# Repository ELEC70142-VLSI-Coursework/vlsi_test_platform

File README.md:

# VLSI Test Platform

A complete hardware and software solution for bringing up and testing the VLSI SoC Project IC. This repository contains the FPGA firmware, Python host tools, and hardware design documentation.

## System Overview

The test platform consists of three integrated components:

<div align="center">
    
</div>

## Directory Structure

```
vlsi_test_platform/
├── gw/                    # FPGA Firmware (DE10-Lite)
│   ├── src/              # SystemVerilog modules
│   │   ├── DE10Top.sv    # Top-level module
│   │   ├── jtag_uart_bridge.sv
│   │   ├── jtag_engine.sv
│   │   ├── adc_commander.sv
│   │   ├── i2c_master.sv
│   │   └── uart_*.sv     # UART controller modules
│   ├── test/             # DUT (Device Under Test) bitstreams
│   └── README.md         # FPGA documentation
│
├── sw/                    # Host-Side Python Tools
│   ├── JTAGProg.py       # JTAG programmer and tester
│   └── README.md         # Python tool documentation
│
├── hw/                    # Test Board PCB Design
│   ├── [Schematic/Layout files]
│   └── README.md         # Hardware documentation
│
└── README.md             # This file
```

## Quick Start

### Prerequisites

1. **Hardware**: DE10-Lite FPGA board and VLSI test board
2. **Software**: Quartus Prime, Python 3.6+, pyserial

### 1. Program the FPGA

1. Load the compiled FPGA design (`.sof` file) onto the DE10-Lite using Quartus Programmer
2. The FPGA automatically configures the test board DAC after reset
3. Verify that the USB-UART bridge is recognized on your host computer

### 2. Program the IC via JTAG

```bash
# Test mode: verify JTAG communication with a known pattern
python JTAGProg.py COM4 --test-mode --word-count 256

# Load mode: program memory from a hex file
python JTAGProg.py COM4 program.hex
```

See [sw/README.md](sw/README.md) for full usage details.

### 3. Verify the Setup

- Check that the test board LEDs indicate correct power and USB connection
- Monitor JTAG read/write throughput in the python interface output
- Inspect the IC power supplies and clock signals with an oscilloscope if needed

## Component Details

### FPGA Firmware (gw/)

The DE10-Lite FPGA implements:
- **UART-to-JTAG Bridge**: Converts serial bytes to JTAG protocol for IC programming
- **I2C Master**: Configures the DAC for PLL bias voltages
- **Clock Generator**: Produces a test clock output

[Read more](gw/README.md)

### Python Host Tool (sw/)

`JTAGProg.py` provides:
- **Test Mode**: Random write/read verification for JTAG communication
- **Load Mode**: Program IC memory from a plain-text hex file
- **Performance Monitoring**: Reports read/write throughput and errors

[Read more](sw/README.md)

### Test Board Hardware (hw/)

The PCB includes:
- PLCC socket for the VLSI IC
- Power management (3.3 V and 1.2 V LDOs)
- DAC for PLL bias voltage tuning
- USB-to-UART bridge (CP2102N)
- FPGA connector for control signals (JTAG, I2C, clock)
- Reset button and DIP switch for PLL frequency selection

[Read more](hw/README.md)

## References

- Altera DE10-Lite Board: [User Manual](https://www.intel.com/content/www/us/en/programmable/documentation/boards/de10_lite_user_manual.pdf)
- CP2102N USB-UART IC: [Datasheet](https://www.silabs.com/documents/public/data-sheets/cp2102n-datasheet.pdf)
- DAC7578 DAC IC: [Datasheet](https://www.ti.com/lit/ds/symlink/dac7578.pdf?ts=1773684272389&ref_url=https%253A%252F%252Fwww.ti.com%252Fproduct%252FDAC7578)

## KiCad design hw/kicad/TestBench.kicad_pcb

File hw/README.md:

# Testboard Hardware

The testboard is an integrated solution for the **VLSI SoC Project** IC bring-up. It includes:

- PLCC socket
- LDOs for the padring and core supplies (3.3 V and 1.2 V respectively)
- Reset button
- Solderable jumper to select active-high or active-low reset
- 25 MHz crystal oscillator
- DAC to supply bias voltages to the PLL
- 4-position DIP switch for selecting the PLL frequency
- USB-to-UART bridge IC (CP2102N)
- Jumpers to select the source of the clock and 1.2 V supply (board or connector)
- Buffers for the FPGA input clock and the board output clock
- Connector for the DE10-Lite FPGA

<div align="center">
    
</div>

## Assembly Guidelines

First, solder the SMD components using the stencil and a reflow oven. Do not place the DIP switch in the reflow oven — solder it by hand afterwards.

Once the SMD components are soldered, test the LDOs by applying 5 V and 3.3 V to connector U1 (TB). Check for shorts on the USB-C connector and verify that QFN packages U5 and U6 have no solder bridges and all pins are properly soldered. 

Set solder jumpers JP4 and JP5 to the low position, marked "L" on the silkscreen.

Next, solder the through-hole components: power switch S2, connector J2, jumpers JP1 and JP2, and the 40-pin FPGA connectors. Do not solder the PLCC socket (J4) at this stage — leaving it unsoldered allows easier access to the pin holes for testing.

Once testing is complete, solder the PLCC socket with the orientation arrow pointing down, indicating pin 1.

### Testing the DAC

The I2C DAC IC can be tested by connecting a DE10-Lite FPGA board and loading the bitstream described elsewhere in this repository. The FPGA automatically configures the DAC over I2C after reset. The DAC requires the 1.2 V supply as its reference — ensure the core-supply jumper is set to "BRD" to use the onboard LDO. Measure the DAC outputs at testpoints DAC1 and DAC2; the expected voltages are defined in [gw/src/adc_commander.sv](../gw/src/adc_commander.sv).

### Testing the USB-UART Bridge

Test the USB-UART bridge using the provided FPGA design (see elsewhere in this repository). After loading the bitstream, verify UART–JTAG communication using the Python script.

The TX/RX LEDs (D2 and D3) will not function on a newly soldered CP2102N until the IC has been configured. To configure it:

1. Install the USB-to-UART VCP drivers from [Silicon Labs](https://www.silabs.com/software-and-tools/usb-to-uart-bridge-vcp-drivers?tab=downloads).
2. Install [Simplicity Studio 5](https://www.silabs.com/software-and-tools/simplicity-studio/simplicity-studio-version-5) (not version 6).
3. Power the board and launch Simplicity Studio — it should detect the CP2102N automatically.
4. Open **Tools > Express Configurator**.
5. Under **Configuration Groupings > Port Configurations > GPIO**, set GPIO0 to "TX Toggle" and GPIO1 to "RX Toggle".
6. Click **Program to Device**.

## Suggested Improvements

Future board revisions could include:

- Decoupling capacitors between the PLCC socket supply pins and ground.
- A silkscreen mark indicating PLCC socket pin 1.
- A small series resistor between the PLCC socket clock input and the Schmitt-trigger buffer to reduce ringing.
- Additional mounting holes.

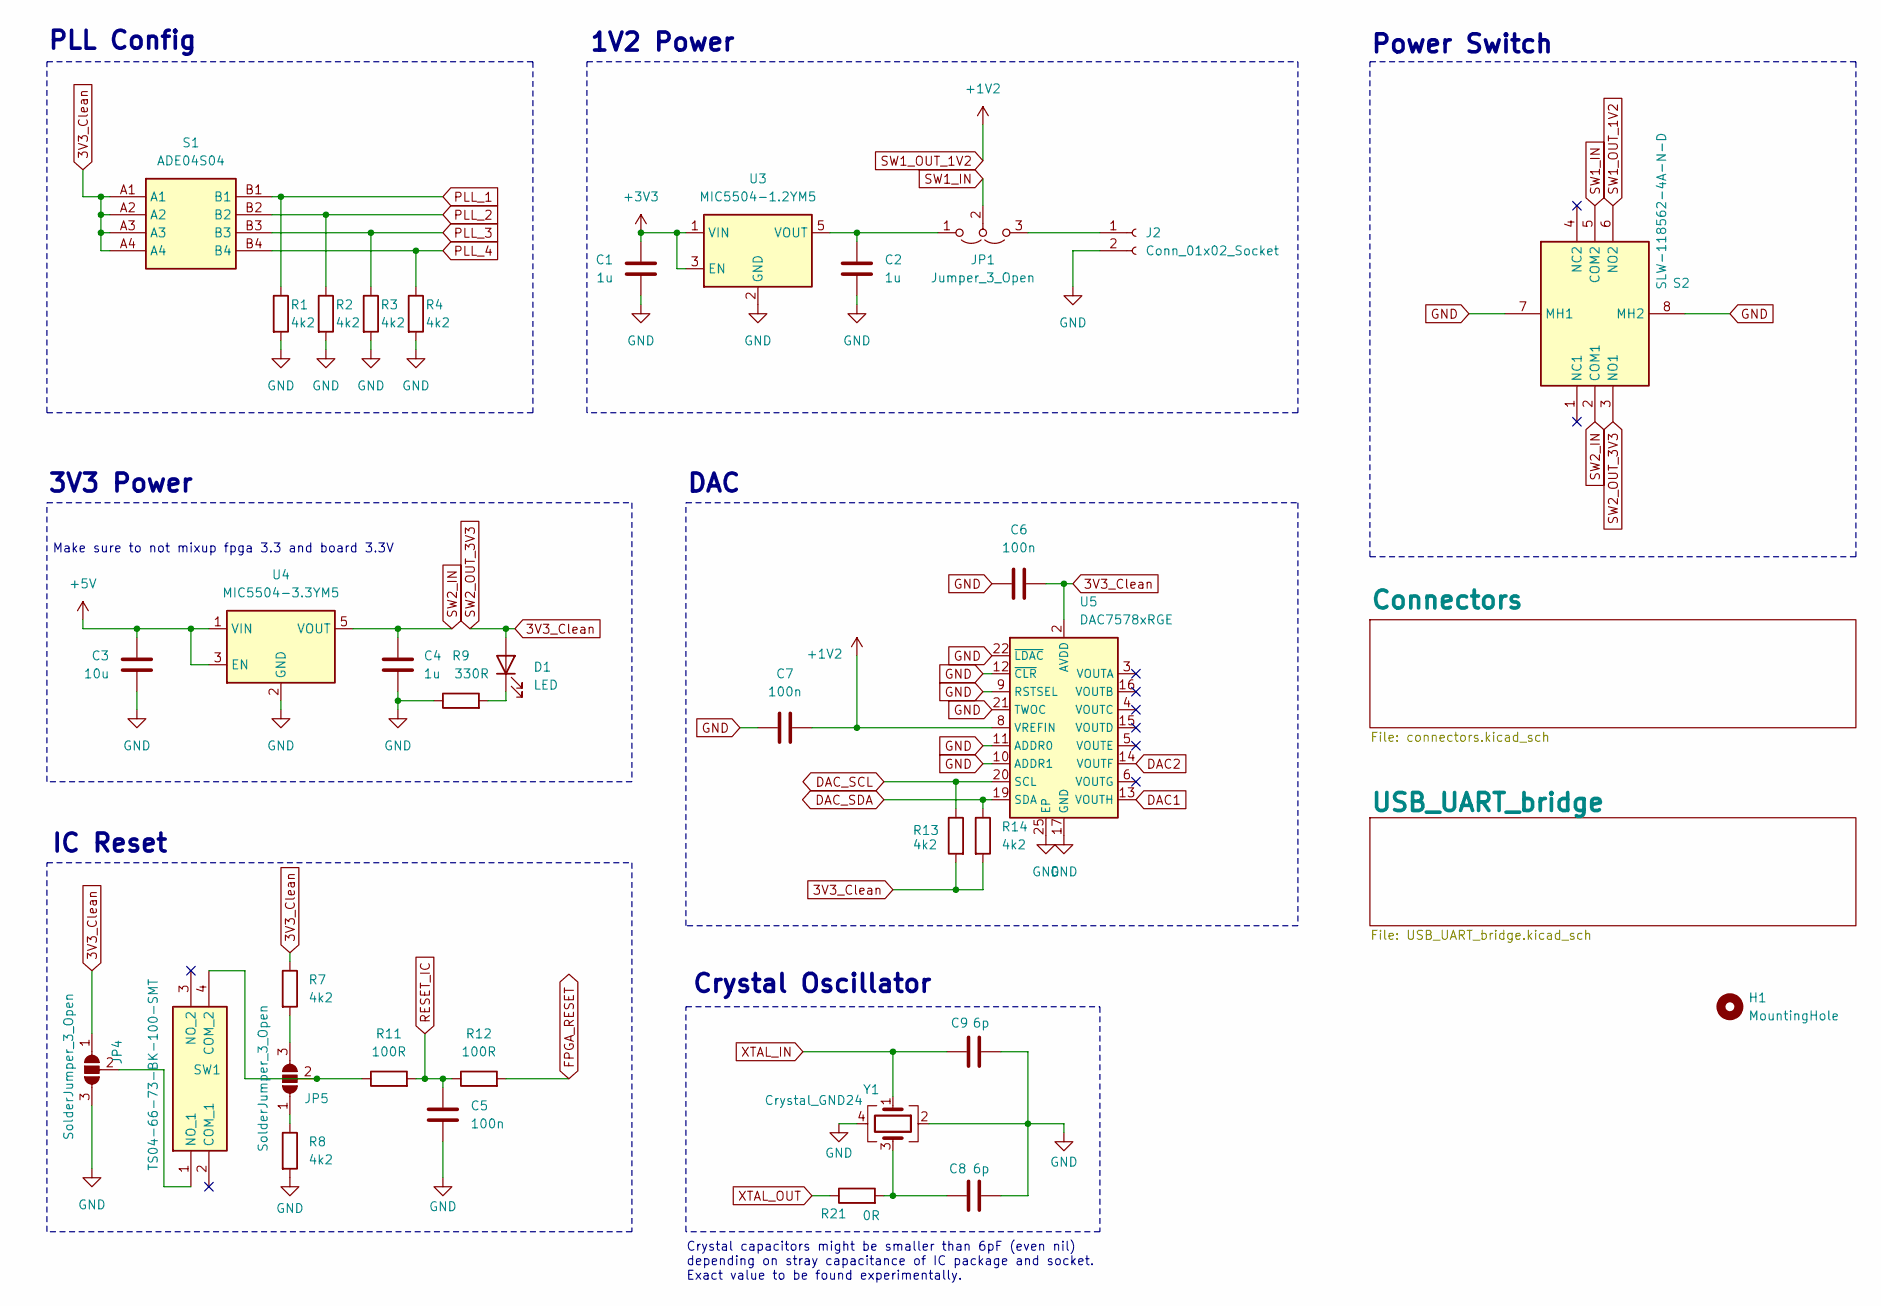
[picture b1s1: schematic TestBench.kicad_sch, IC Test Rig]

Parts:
C1, C2, C4: 1u; C_0805_2012Metric_Pad1.18x1.45mm_HandSolder
C3: 10u; C_0805_2012Metric_Pad1.18x1.45mm_HandSolder
C5, C6, C7: 100n; C_0805_2012Metric_Pad1.18x1.45mm_HandSolder
C8, C9: 6p; C_0805_2012Metric_Pad1.18x1.45mm_HandSolder
D1: LED; LED_0805_2012Metric_Pad1.15x1.40mm_HandSolder
H1: MountingHole; MountingHole_3.2mm_M3
J2: Conn_01x02_Socket; CTB30512BK
JP1: Jumper_3_Open; PinHeader_1x03_P2.54mm_Vertical
JP4, JP5: SolderJumper_3_Open; SolderJumper-3_P1.3mm_Open_RoundedPad1.0x1.5mm
R1, R2, R3, R4, R7, R8, R13, R14: 4k2; R_0805_2012Metric_Pad1.20x1.40mm_HandSolder
R9: 330R; R_0805_2012Metric_Pad1.20x1.40mm_HandSolder
R11, R12: 100R; R_0805_2012Metric_Pad1.20x1.40mm_HandSolder
R21: 0R; R_0805_2012Metric_Pad1.20x1.40mm_HandSolder
S1: ADE04S04; Mouser Part Number 506-ADE04S04
S2: SLW-118562-4A-N-D; SLW1185624AND; Mouser Part Number 179-SLW1185624AND
SW1: TS04-66-73-BK-100-SMT; TS046665BK160SMT; Mouser Part Number 179-TS046673BK100SMT
U3: MIC5504-1.2YM5; SOT-23-5
U4: MIC5504-3.3YM5; SOT-23-5
U5: DAC7578xRGE; QFN-24-1EP_4x4mm_P0.5mm_EP2.6x2.6mm
Y1: Crystal_GND24; Crystal_SMD_3225-4Pin_3.2x2.5mm

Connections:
3V3_Clean: C6.2, D1.2 (A), JP4.1 (A), R7.1, R13.2, R14.2, S1.A1, S1.A2, S1.A3, S1.A4, S2.3 (NO1), U5.2 (AVDD); also elsewhere on the board
+3V3: C1.1, U3.1 (VIN), U3.3 (EN); also elsewhere on the board
+5V: C3.1, U4.1 (VIN), U4.3 (EN); also elsewhere on the board
DAC1: U5.13 (VOUTH); also elsewhere on the board
DAC2: U5.14 (VOUTF); also elsewhere on the board
DAC_SCL: R13.1, U5.20 (SCL); also elsewhere on the board
DAC_SDA: R14.1, U5.19 (SDA); also elsewhere on the board
FPGA_RESET: R12.2; also elsewhere on the board
GND: C1.2, C2.2, C3.2, C4.2, C5.2, C6.1, C7.1, C8.2, C9.2, J2.2, JP4.3 (B), R1.2, R2.2, R3.2, R4.2, R8.2, R9.1, S2.7 (MH1), S2.8 (MH2), U3.2 (GND), U4.2 (GND), U5.9 (RSTSEL), U5.10 (ADDR1), U5.11 (ADDR0), U5.12 (~CLR), U5.17 (GND), U5.21 (TWOC), U5.22 (~LDAC), U5.25 (EP), Y1.2, Y1.4; also elsewhere on the board
unnamed: C8.1, R21.2, Y1.3
unnamed: D1.1 (K), R9.2
unnamed: J2.1, JP1.3 (B)
unnamed: C2.1, JP1.1 (A), U3.5 (VOUT)
unnamed: JP4.2 (C), SW1.1 (NO_1)
unnamed: JP5.1 (A), R8.1
unnamed: JP5.3 (B), R7.2
unnamed: JP5.2 (C), R11.1, SW1.4 (COM_2)
PLL_1: R1.1, S1.B1; also elsewhere on the board
PLL_2: R2.1, S1.B2; also elsewhere on the board
PLL_3: R3.1, S1.B3; also elsewhere on the board
PLL_4: R4.1, S1.B4; also elsewhere on the board
RESET_IC: C5.1, R11.2, R12.1; also elsewhere on the board
SW1_IN: JP1.2 (C), S2.5 (COM2)
SW1_OUT_1V2: C7.2, S2.6 (NO2), U5.8 (VREFIN); also elsewhere on the board
SW2_IN: C4.1, S2.2 (COM1), U4.5 (VOUT)
XTAL_IN: C9.1, Y1.1; also elsewhere on the board
XTAL_OUT: R21.1; also elsewhere on the board

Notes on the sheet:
DAC
Make sure to not mixup fpga 3.3 and board 3.3V
3V3 Power
Crystal capacitors might be smaller than 6pF (even nil) depending on stray capacitance of IC package and socket. Exact value to be found experimentally.
Power Switch
Crystal Oscillator
1V2 Power
IC Reset
PLL Config

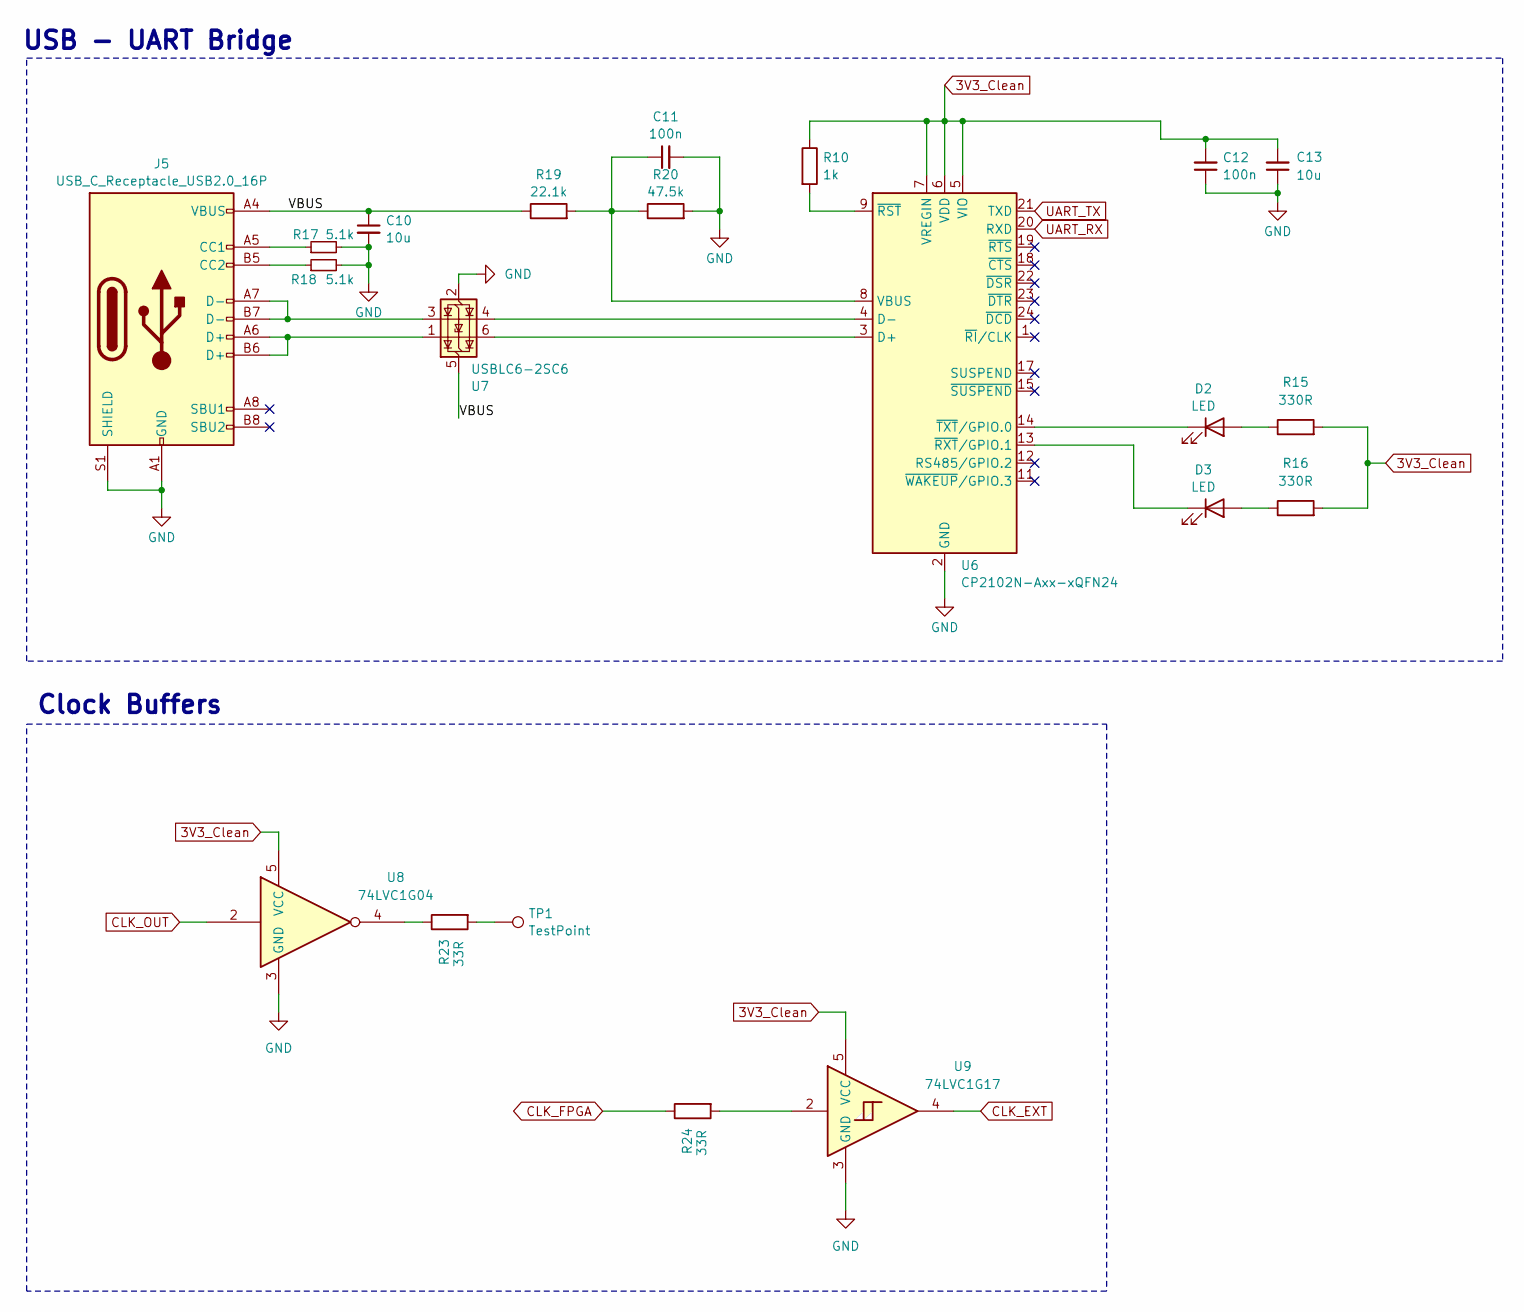
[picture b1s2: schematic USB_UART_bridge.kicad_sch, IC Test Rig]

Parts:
C10, C13: 10u; C_0805_2012Metric_Pad1.18x1.45mm_HandSolder
C11, C12: 100n; C_0805_2012Metric_Pad1.18x1.45mm_HandSolder
D2, D3: LED; LED_0805_2012Metric_Pad1.15x1.40mm_HandSolder
J5: USB_C_Receptacle_USB2.0_16P; USB_C_Receptacle_GCT_USB4105-xx-A_16P_TopMnt_Horizontal
R10: 1k; R_0805_2012Metric_Pad1.20x1.40mm_HandSolder
R15, R16: 330R; R_0805_2012Metric_Pad1.20x1.40mm_HandSolder
R17, R18: 5.1k; R_0805_2012Metric_Pad1.20x1.40mm_HandSolder
R19: 22.1k; R_0805_2012Metric_Pad1.20x1.40mm_HandSolder
R20: 47.5k; R_0805_2012Metric_Pad1.20x1.40mm_HandSolder
R23, R24: 33R; R_0805_2012Metric_Pad1.20x1.40mm_HandSolder
TP1: TestPoint; TestPoint_Pad_D1.0mm
U6: CP2102N-Axx-xQFN24; QFN-24-1EP_4x4mm_P0.5mm_EP2.6x2.6mm
U7: USBLC6-2SC6; SOT-23-6
U8: 74LVC1G04; SOT-353_SC-70-5
U9: 74LVC1G17; SOT-353_SC-70-5

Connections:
3V3_Clean: C12.2, C13.2, R10.1, R15.2, R16.2, U6.5 (VIO), U6.6 (VDD), U6.7 (VREGIN), U8.5 (VCC), U9.5 (VCC); also elsewhere on the board
/USB_UART_bridge/VBUS: C10.1, J5.A4 (VBUS), J5.A9 (VBUS), J5.B4 (VBUS), J5.B9 (VBUS), R19.1, U7.5 (VBUS)
CLK_EXT: U9.4; also elsewhere on the board
CLK_FPGA: R24.1; also elsewhere on the board
CLK_OUT: U8.2; also elsewhere on the board
GND: C10.2, C11.2, C12.1, C13.1, J5.A1 (GND), J5.A12 (GND), J5.B1 (GND), J5.B12 (GND), J5.S1 (SHIELD), R17.2, R18.2, R20.2, U6.2 (GND), U6.25 (GND), U7.2 (GND), U8.3 (GND), U9.3 (GND); also elsewhere on the board
unnamed: D2.2 (A), R15.1
unnamed: D2.1 (K), U6.14 (~TXT/GPIO.0)
unnamed: D3.2 (A), R16.1
unnamed: D3.1 (K), U6.13 (~RXT/GPIO.1)
unnamed: J5.A5 (CC1), R17.1
unnamed: J5.B5 (CC2), R18.1
unnamed: J5.A6 (D+), J5.B6 (D+), U7.1 (I/O1)
unnamed: J5.A7 (D-), J5.B7 (D-), U7.3 (I/O2)
unnamed: R23.1, U8.4
unnamed: R23.2, TP1.1
unnamed: R24.2, U9.2
unnamed: U6.3 (D+), U7.6 (I/O1)
unnamed: U6.4 (D-), U7.4 (I/O2)
unnamed: C11.1, R19.2, R20.1, U6.8 (VBUS)
unnamed: R10.2, U6.9 (~RST)
UART_RX: U6.20 (RXD); also elsewhere on the board
UART_TX: U6.21 (TXD); also elsewhere on the board

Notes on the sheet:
Clock Buffers
USB - UART Bridge

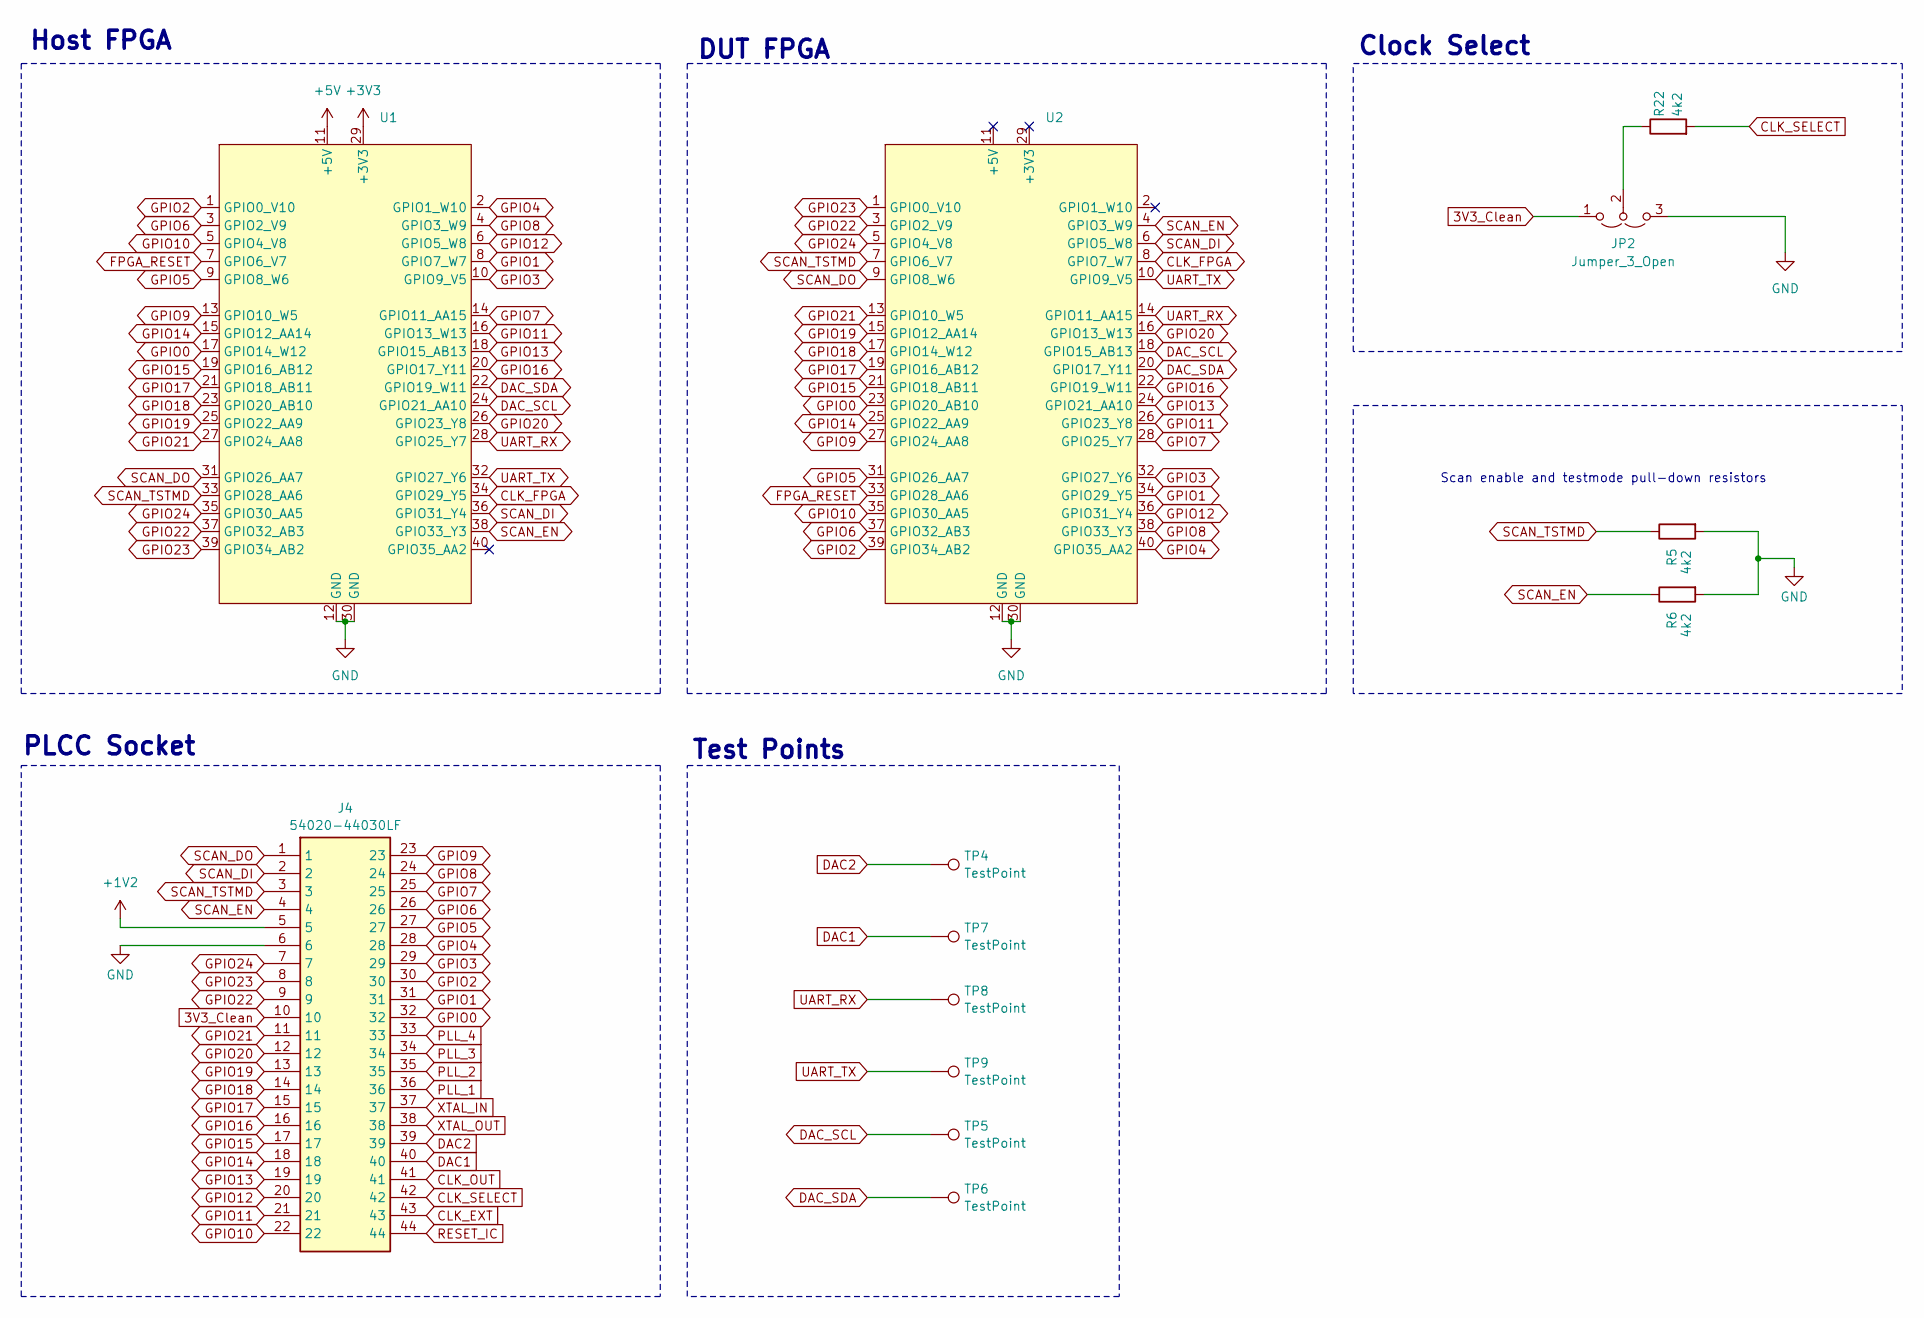
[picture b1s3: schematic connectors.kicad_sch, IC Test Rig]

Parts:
J4: 54020-44030LF; 5402044030LF; Manufacturer_Part_Number 54020-44030LF
JP2: Jumper_3_Open; PinHeader_1x03_P2.54mm_Vertical
R5, R6, R22: 4k2; R_0805_2012Metric_Pad1.20x1.40mm_HandSolder
TP4, TP5, TP6, TP7, TP8, TP9: TestPoint; TestPoint_Pad_D1.0mm
U1, U2: PinHeader_2x20_P2.54mm_Vertical

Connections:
3V3_Clean: J4.10, JP2.1 (A); also elsewhere on the board
+3V3: U1.29 (+3V3); also elsewhere on the board
+5V: U1.11 (+5V); also elsewhere on the board
CLK_EXT: J4.43; also elsewhere on the board
CLK_FPGA: U1.34 (GPIO29_Y5), U2.8 (GPIO7_W7); also elsewhere on the board
CLK_OUT: J4.41; also elsewhere on the board
CLK_SELECT: J4.42, R22.2
DAC1: J4.40, TP7.1; also elsewhere on the board
DAC2: J4.39, TP4.1; also elsewhere on the board
DAC_SCL: TP5.1, U1.24 (GPIO21_AA10), U2.18 (GPIO15_AB13); also elsewhere on the board
DAC_SDA: TP6.1, U1.22 (GPIO19_W11), U2.20 (GPIO17_Y11); also elsewhere on the board
FPGA_RESET: U1.7 (GPIO6_V7), U2.33 (GPIO28_AA6); also elsewhere on the board
GND: J4.6, JP2.3 (B), R5.2, R6.2, U1.12 (GND), U1.30 (GND), U2.12 (GND), U2.30 (GND); also elsewhere on the board
GPIO0: J4.32, U1.17 (GPIO14_W12), U2.23 (GPIO20_AB10)
GPIO1: J4.31, U1.8 (GPIO7_W7), U2.34 (GPIO29_Y5)
GPIO2: J4.30, U1.1 (GPIO0_V10), U2.39 (GPIO34_AB2)
GPIO3: J4.29, U1.10 (GPIO9_V5), U2.32 (GPIO27_Y6)
GPIO4: J4.28, U1.2 (GPIO1_W10), U2.40 (GPIO35_AA2)
GPIO5: J4.27, U1.9 (GPIO8_W6), U2.31 (GPIO26_AA7)
GPIO6: J4.26, U1.3 (GPIO2_V9), U2.37 (GPIO32_AB3)
GPIO7: J4.25, U1.14 (GPIO11_AA15), U2.28 (GPIO25_Y7)
GPIO8: J4.24, U1.4 (GPIO3_W9), U2.38 (GPIO33_Y3)
GPIO9: J4.23, U1.13 (GPIO10_W5), U2.27 (GPIO24_AA8)
GPIO10: J4.22, U1.5 (GPIO4_V8), U2.35 (GPIO30_AA5)
GPIO11: J4.21, U1.16 (GPIO13_W13), U2.26 (GPIO23_Y8)
GPIO12: J4.20, U1.6 (GPIO5_W8), U2.36 (GPIO31_Y4)
GPIO13: J4.19, U1.18 (GPIO15_AB13), U2.24 (GPIO21_AA10)
GPIO14: J4.18, U1.15 (GPIO12_AA14), U2.25 (GPIO22_AA9)
GPIO15: J4.17, U1.19 (GPIO16_AB12), U2.21 (GPIO18_AB11)
GPIO16: J4.16, U1.20 (GPIO17_Y11), U2.22 (GPIO19_W11)
GPIO17: J4.15, U1.21 (GPIO18_AB11), U2.19 (GPIO16_AB12)
GPIO18: J4.14, U1.23 (GPIO20_AB10), U2.17 (GPIO14_W12)
GPIO19: J4.13, U1.25 (GPIO22_AA9), U2.15 (GPIO12_AA14)
GPIO20: J4.12, U1.26 (GPIO23_Y8), U2.16 (GPIO13_W13)
GPIO21: J4.11, U1.27 (GPIO24_AA8), U2.13 (GPIO10_W5)
GPIO22: J4.9, U1.37 (GPIO32_AB3), U2.3 (GPIO2_V9)
GPIO23: J4.8, U1.39 (GPIO34_AB2), U2.1 (GPIO0_V10)
GPIO24: J4.7, U1.35 (GPIO30_AA5), U2.5 (GPIO4_V8)
unnamed: JP2.2 (C), R22.1
PLL_1: J4.36; also elsewhere on the board
PLL_2: J4.35; also elsewhere on the board
PLL_3: J4.34; also elsewhere on the board
PLL_4: J4.33; also elsewhere on the board
RESET_IC: J4.44; also elsewhere on the board
SCAN_DI: J4.2, U1.36 (GPIO31_Y4), U2.6 (GPIO5_W8)
SCAN_DO: J4.1, U1.31 (GPIO26_AA7), U2.9 (GPIO8_W6)
SCAN_EN: J4.4, R6.1, U1.38 (GPIO33_Y3), U2.4 (GPIO3_W9)
SCAN_TSTMD: J4.3, R5.1, U1.33 (GPIO28_AA6), U2.7 (GPIO6_V7)
SW1_OUT_1V2: J4.5; also elsewhere on the board
UART_RX: TP8.1, U1.28 (GPIO25_Y7), U2.14 (GPIO11_AA15); also elsewhere on the board
UART_TX: TP9.1, U1.32 (GPIO27_Y6), U2.10 (GPIO9_V5); also elsewhere on the board
XTAL_IN: J4.37; also elsewhere on the board
XTAL_OUT: J4.38; also elsewhere on the board

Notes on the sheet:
Host FPGA
Clock Select
DUT FPGA
Test Points
Scan enable and testmode pull-down resistors
PLCC Socket

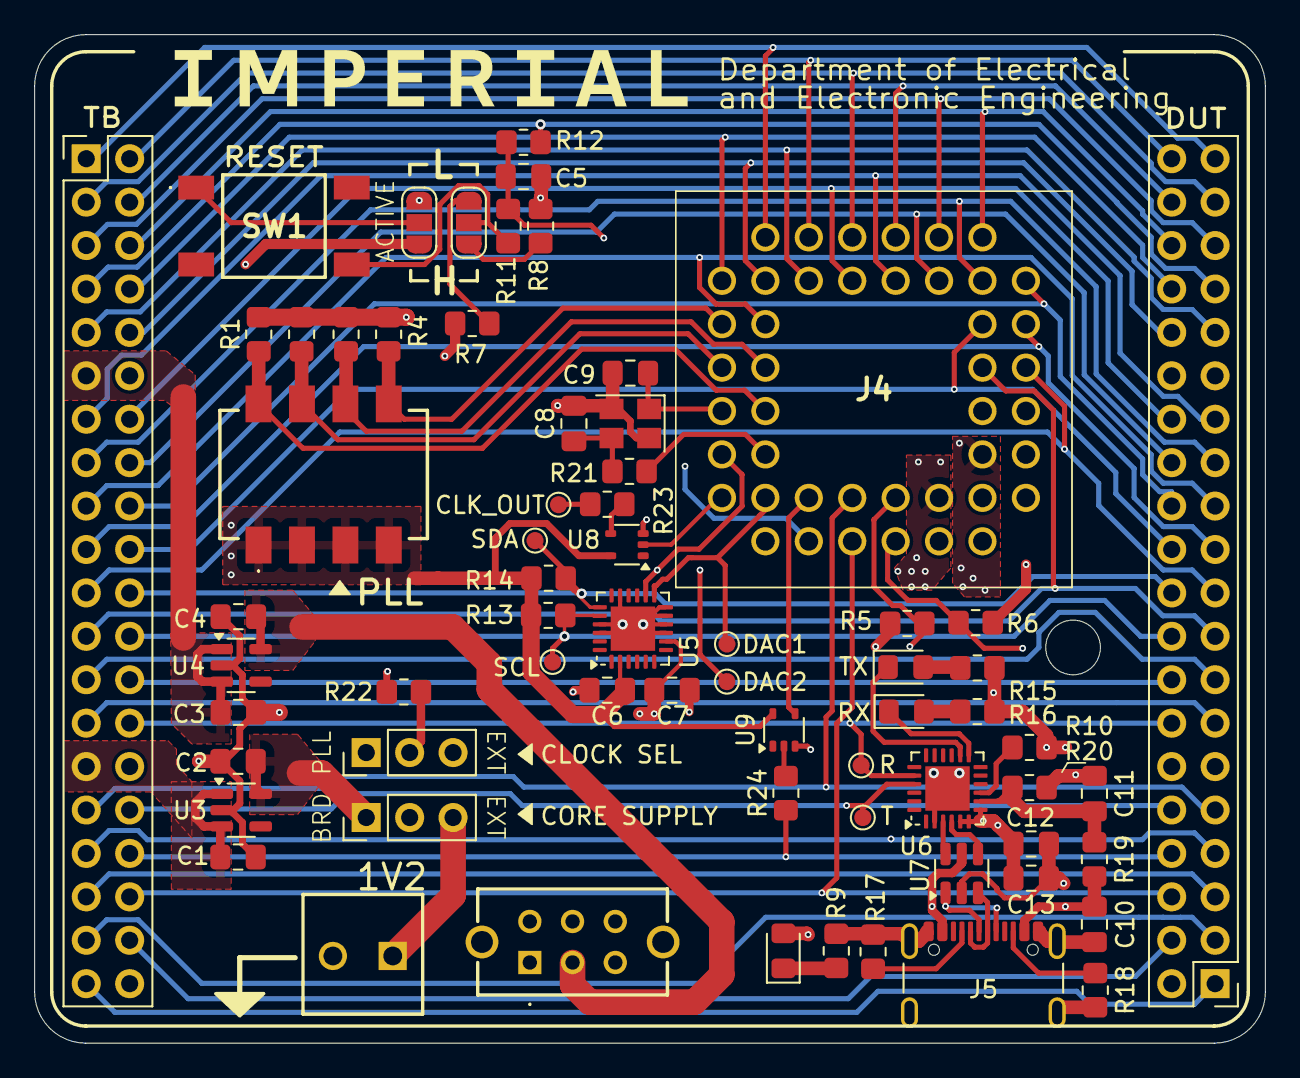
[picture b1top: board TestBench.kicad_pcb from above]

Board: 4 copper layers, 72.0 x 59.0 mm, 68 parts (0 on the bottom side), 79 nets.

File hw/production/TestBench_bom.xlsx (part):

|  |  |  |  |  |  |  |  |  |  | 10
 | Reference | Value | Footprint | Qty | Supplier | Other Supplier | SupplierPartNo | Description | UnitPrice | MinQty | Quantity | LineSum | Link
 | C1,C2,C4 | 1u | Capacitor_SMD:C_0805_2012Metric_Pad1.18x1.45mm_HandSolder | 3 | OneCall (Farnell and CPC) |  | 3013482 | £0.0679 - SMD Multilayer Ceramic Capacitor, 1 µF, 50 V, 0805 [2012 Metric], ± 1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 | 4.6977999999999999E-2 | 10 | 30 | 1.40934 | https://uk.farnell.com/samsung-electro-mechanics/cl21b105kbf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
 | C3,C10,C13 | 10u | Capacitor_SMD:C_0805_2012Metric_Pad1.18x1.45mm_HandSolder | 3 | OneCall (Farnell and CPC) |  | 3013485 | £0.1488 - SMD Multilayer Ceramic Capacitor, 10 µF, 16 V, 0805 [2012 Metric], ± 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 | 0.10292 | 10 | 30 | 3.0876000000000001 | https://uk.farnell.com/samsung-electro-mechanics/cl21b106koq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
 | C5,C6,C7,C11,C12 | 100n | Capacitor_SMD:C_0805_2012Metric_Pad1.18x1.45mm_HandSolder | 5 | OneCall (Farnell and CPC) |  | 4539029 | £0.0329 - SMD Multilayer Ceramic Capacitor, 0.1 µF, 50 V, 0805 [2012 Metric], ±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 | 1.3114000000000001E-2 | 10 | 50 | 0.65570000000000006 | https://uk.farnell.com/samsung-electro-mechanics/cl21b104kbc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
 | C8,C9 | 6p | Capacitor_SMD:C_0805_2012Metric_Pad1.18x1.45mm_HandSolder | 2 | OneCall (Farnell and CPC) |  | 1759185 | £0.054 - SMD Multilayer Ceramic Capacitor, 6 pF, 50 V, 0805 [2012 Metric], ± 0.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 | 5.3999999999999999E-2 | 10 | 20 | 1.08 | https://uk.farnell.com/multicomp-pro/mc0805n6r0d500ct/cap-6p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
 | D1,D2,D3 | LED | LED_SMD:LED_0805_2012Metric_Pad1.15x1.40mm_HandSolder | 3 | OneCall (Farnell and CPC) |  | 1226392 | £0.1548 - LED, Hyper-Bright, Red, SMD, 0805 [2012 Metric], 25 mA, 2 V, 633 nm | 0.108 | 10 | 30 | 3.2399999999999998 | https://uk.farnell.com/osram-opto-semiconductors/lsr976/led-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
 | J2 | Conn_01x02_Socket | Footprints:CTB30512BK | 1 | OneCall (Farnell and CPC) |  | 3882615 | £0.5508 - Wire-To-Board Terminal Block, 3.5 mm, 2 Ways, 1 mm², Screw | 0.55079999999999996 | 1 | 10 | 5.5079999999999991 | https://uk.farnell.com/camdenboss/ctb3051-2bk/terminal-block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
 | J4 | 54020-44030LF | Footprints:5402044030LF | 1 | OneCall (Farnell and CPC) |  | 3881743 | £2.55 - IC & Component Socket, 44 Contacts, PLCC Socket, 2.54 mm, FCI 54020 Ser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 | 2.5499999999999998 | 1 | 10 | 25.5 | https://uk.farnell.com/amphenol-fci/54020-44030lf/conn-plcc-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
 | J5 | USB_C_Receptacle_USB2.0_16P | Connector_USB:USB_C_Receptacle_GCT_USB4105-xx-A_16P_TopMnt_Horizontal | 1 | OneCall (Farnell and CPC) |  | 3588205 | £0.744 - USB Connector, 5A, 48V, 240W, USB Type C, USB 2.0, Receptacle, 16 Ways | 0.74399999999999999 | 1 | 10 | 7.4399999999999995 | https://uk.farnell.com/gct-global-connector-technology/usb41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
 | R1,R2,R3,R4,R5,R6,R7,R8,R13,R14,R22 | 4k2 | Resistor_SMD:R_0805_2012Metric_Pad1.20x1.40mm_HandSolder | 11 | OneCall (Farnell and CPC) |  | 3952297 | £0.012 - SMD Chip Resistor, 4.3 kohm, ± 5%, 125 mW, 0805 [2012 Metric], Thick F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 | 8.0000000000000002E-3 | 10 | 110 | 0.88 | https://uk.farnell.com/yageo/rc0805jr-074k3l/res-4k3-5-0-125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
 | R9,R15,R16 | 330R | Resistor_SMD:R_0805_2012Metric_Pad1.20x1.40mm_HandSolder | 1 | OneCall (Farnell and CPC) |  | 2447638 | £0.0156 - SMD Chip Resistor, 330 ohm, ± 1%, 125 mW, 0805 [2012 Metric], Thick F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 | 1.5599999999999999E-2 | 10 | 10 | 0.156 | https://uk.farnell.com/multicomp-pro/mcwr08x3300ftl/res-330r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
 | R23, R24 | 33R | Resistor_SMD:R_0805_2012Metric_Pad1.20x1.40mm_HandSolder | 1 | OneCall (Farnell and CPC) |  | 2447640 | £0.0156 - SMD Chip Resistor, 33 ohm, ± 1%, 125 mW, 0805 [2012 Metric], Thick Fi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 | 1.5599999999999999E-2 | 10 | 10 | 0.156 | https://uk.farnell.com/multicomp-pro/mcwr08x33r0ftl/res-33r-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
 | R10 | 1k | Resistor_SMD:R_0805_2012Metric_Pad1.20x1.40mm_HandSolder | 1 | OneCall (Farnell and CPC) |  | 2447587 | £0.0156 - SMD Chip Resistor, 1 kohm, ± 1%, 125 mW, 0805 [2012 Metric], Thick Fi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 | 1.5599999999999999E-2 | 10 | 10 | 0.156 | https://uk.farnell.com/multicomp-pro/mcwr08x1001ftl/res-1k-1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
 | R11,R12 | 100R | Resistor_SMD:R_0805_2012Metric_Pad1.20x1.40mm_HandSolder | 2 | OneCall (Farnell and CPC) |  | 9332375 | £0.0139 - SMD Chip Resistor, 100 ohm, ± 1%, 100 mW, 0805 [2012 Metric], Thick F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 | 9.2800000000000001E-3 | 10 | 20 | 0.18559999999999999 | https://uk.farnell.com/multicomp-pro/mc01w08051100r/res-100r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
 | R17,R18 | 5.1k | Resistor_SMD:R_0805_2012Metric_Pad1.20x1.40mm_HandSolder | 2 | OneCall (Farnell and CPC) |  | 2447692 | £0.0156 - SMD Chip Resistor, 5.1 kohm, ± 1%, 125 mW, 0805 [2012 Metric], Thick 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 | 1.5599999999999999E-2 | 10 | 20 | 0.312 | https://uk.farnell.com/multicomp-pro/mcwr08x5101ftl/res-5k1-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
 | R19 | 22.1k | Resistor_SMD:R_0805_2012Metric_Pad1.20x1.40mm_HandSolder | 1 | OneCall (Farnell and CPC) |  | 2447607 | £0.0156 - SMD Chip Resistor, 22 kohm, ± 1%, 125 mW, 0805 [2012 Metric], Thick F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 | 1.5599999999999999E-2 | 10 | 10 | 0.156 | https://uk.farnell.com/multicomp-pro/mcwr08x2202ftl/res-22k-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
 | R20 | 47.5k | Resistor_SMD:R_0805_2012Metric_Pad1.20x1.40mm_HandSolder | 1 | OneCall (Farnell and CPC) |  | 2447665 | £0.0156 - SMD Chip Resistor, 47.5 kohm, ± 1%, 125 mW, 0805 [2012 Metric], Thick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 | 1.5599999999999999E-2 | 10 | 10 | 0.156 | https://uk.farnell.com/multicomp-pro/mcwr08x4752ftl/res-47k5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
 | R21 | 0R | Resistor_SMD:R_0805_2012Metric_Pad1.20x1.40mm_HandSolder | 1 | OneCall (Farnell and CPC) |  | 4312018 | £0.0139 - Zero Ohm Resistor, Jumper, 0805 [2012 Metric], Thick Film, 125 mW, 2 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 | 9.2800000000000001E-3 | 10 | 10 | 9.2799999999999994E-2 | https://uk.farnell.com/yageo/rc0805fr-130rl/res-2a-0-125w-th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
 | U4 | MIC5504-3.3YM5 | Package_TO_SOT_SMD:SOT-23-5 | 1 | OneCall (Farnell and CPC) |  | 2510377 | £0.144 - Fixed LDO Voltage Regulator, 2.5V to 5.5V, 160mV Dropout, 3.3Vout, 300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 | 0.14399999999999999 | 1 | 10 | 1.44 | https://uk.farnell.com/microchip/mic5504-3-3ym5-tr/ldo-fixed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
 | U6 | CP2102N-Axx-xQFN24 | Package_DFN_QFN:QFN-24-1EP_4x4mm_P0.5mm_EP2.6x2.6mm | 1 | OneCall (Farnell and CPC) |  | 3013847 | £3.22 - Interface Bridges, USB to UART, 3 V, 3.6 V, QFN, 24 Pins, -40 °C | 3.22 | 1 | 10 | 32.200000000000003 | https://uk.farnell.com/silicon-labs/cp2102n-a02-gqfn24/usb-t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
 | U7 | USBLC6-2SC6 | Package_TO_SOT_SMD:SOT-23-6 | 1 | OneCall (Farnell and CPC) |  | 1269406 | £0.368 - ESD Protection Device, 17 V, SOT-23, 6 Pins | 0.36840000000000001 | 1 | 10 | 3.6840000000000002 | https://uk.farnell.com/stmicroelectronics/usblc6-2sc6/esd-pr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
 | U8 | 74LVC1G04 | Package_TO_SOT_SMD:SOT-353_SC-70-5 | 1 | OneCall (Farnell and CPC) |  | 1845218 | £0.016 - Logic IC, Inverter, Single, 1 Inputs, 5 Pins, SOT-353, 74LVC1G04 | 0.1016 | 1 | 10 | 1.016 | https://uk.farnell.com/diodes-inc/74lvc1g04se-7/logic-invert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
 | U9 | 74LVC1G17 | Package_TO_SOT_SMD:SOT-353_SC-70-5 | 1 | OneCall (Farnell and CPC) |  | 1893834 | £0.1034 - Schmitt Trigger Buffer, LVC Family, 1 Input, 32 mA, Totem Pole, 1.65V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 | 0.10349999999999999 | 1 | 10 | 1.0349999999999999 | https://uk.farnell.com/diodes-inc/74lvc1g17se-7/logic-schmit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
 | Y1 | Crystal_GND24 | Crystal:Crystal_SMD_3225-4Pin_3.2x2.5mm | 1 | OneCall (Farnell and CPC) |  | 3819756 | £0.6048 - Crystal, 25 MHz, SMD, 3.2mm x 2.5mm, 20 ppm, 8 pF, 10 ppm, ABM8W Seri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 | 0.6048 | 1 | 10 | 6.048 | https://uk.farnell.com/abracon/abm8w-25-0000mhz-8-d1x-t3/cry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
 | S1 | ADE04S04 | Footprints:ADE04S04 | 1 | Other Supplier: Digikey | Digikey | 450-2040-ND | £1.18 - SWITCH SLIDE DIP SPST 0.1A 24V | 1.18 | 1 | 10 | 11.799999999999999 | https://www.digikey.co.uk/en/products/detail/te-connectivity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
 | S2 | SLW-118562-4A-N-D | Footprints:SLW1185624AND | 1 | Other Supplier: Digikey | Digikey | 2223-SLW-118562-4A-N-D-ND | £0.42 - 11.1 X 8.5 X 6.2 MM, 4 MM RAISED | 0.42 | 1 | 10 | 4.2 | https://www.digikey.at/en/products/detail/same-sky-formerly-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
 | SW1 | TS04-66-73-BK-100-SMT | Footprints:TS046665BK160SMT | 1 | Other Supplier: Digikey | Digikey | 2223-TS04-66-65-BK-160-SMT-ND | £0.13 - SWITCH TACTILE SPST-NO 0.05A 12V | 0.13 | 1 | 10 | 1.3 | https://www.digikey.co.uk/en/products/detail/same-sky-former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

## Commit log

2026-03-11 added hw README
2026-03-11 hw README cleaned up
2026-03-11 adjusted python programming API
2026-03-11 sw README file
2026-03-11 removed sw test files
2026-03-11 added test dut fpga bitstream files
2026-03-12 adjusted adc commander
2026-03-13 working commit
2026-03-13 top module cleanup
2026-03-16 completed READMEs. Added output clock on FPGA topmodule. Updated bitstream files
2026-03-16 cleanup and reference added
2026-03-16 minor additions
2026-03-26 added board components reference view pdf
